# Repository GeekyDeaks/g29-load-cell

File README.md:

# G29 Load Cell Mod

Modification to replace the stock brake pedal sensor on a Logitech G29 pedal set with a load cell,
the purpose of which is to more closely simulate a real brake system which is dependent on
the force applied to the pedal and not the pedal position

I assume this would work on the G920 without any issues, and possibly the G27 and G25,
however I have not had the opportunity to test.

It uses a cheap load cell with two closely matched 1k resistors arranged in a
[Wheatstone bridge](https://en.wikipedia.org/wiki/Wheatstone_bridge)
and an Instrumentation Op-Amp.  The cell is mounted in a 3D printed
model that replaces the lower half of the brake piston assembly

There is a digital version by [SkiDude88](https://github.com/Skidude88/Skidude88-G29-PS4-LoadCell-Arduino/wiki) 
using an HX711, that often comes bundled with the load cells, and an Arduino

Assembly re-uses the spring and rubber block, along with a short piece of M10 rod.
The adjustment of the location of the washer and the protrusion of the top nut
allow changes to the first stage of the pedal, which is designed to simulate
the initial feel of the pedal as the pads move into contact with the disc.

Fully installed, with the amplifier circuit mounted in a small case

2020-10-22 UPDATE

Working on a 3D printed plunger to remove the need to cobble one together

# Shopping list

1. 3D printer capable of 80mm x 43mm x 43mm
2. Bathroom scale type loadcells
3. PCB copper board or stripboard (35mm x 30mm)
4. INA122P instrumentation amplifier
5. 1k trim pot
6. 10ohm trim pot 
7. 2x 1k resistor
8. 100ohm resistor (fake clutch)
9. 900ohm resistor (fake clutch)
10. M10 thread ~30mm
11. 3x Half height M10 nuts
12. 1x M10 nut
13. M10 to 24mm washer

# Software used

1. EAGLE https://www.autodesk.co.uk/products/eagle/free-download
2. Fusion 360 https://www.autodesk.com/campaigns/fusion-360-for-hobbyists

# Load Cells

The load cells are cheap bathroom scale variety.  I got mine from Amazon:

https://www.amazon.co.uk/gp/product/B07TWLP3X8

Each cell is comprised of two resistors one which increases under load (white) and the 
other which decreases (black).  Zero load is approx 1k, with about 2-3 Ohm change under heavy load

# Amplifier Circuit

The loadcell is connected to the circuit as follows:

1. Red -> 3.3v
2. Black -> V+
3. White -> V-

Since we need to output a higher voltage with no load on the cells 
we have to unbalance the bridge so that load brings it back into balance.

The 1k resistors for `R1` and `R2` should be measured and the larger of the two should
be used for `R1` to allow `R_BAL1` to adjust the link with `R2` and force the bridge out of 
balance with no load

`R_REF` should be replaced with a link from the middle pin to the right pin.  This
will tie the `REF` pin on the INA122P to ground.
It was originally used when the design had two load cells
and the INA122P was inverting the gain.

Astute observers may have noticed the connections for the loadcell appear to be
reversed in reference to V+ and V-.  This is because the labelling on the PCB of 
V+ and V- was in reference to the dual load cell configuration and hence the 
labels on the PCB are not correct for a single cell.

## Clutch

The circuit also allows for simulating a clutch, allowing it to be removed if desired.
The G29 has been known to glitch if the clutch is disconnected and the leads left hanging.

If you do not need this feature, you can leave `R3` and `R4` unpopulated on the board

# PCB

The PCB design is a little tricky to manually etch, so we came up with a slightly
larger design to help.  Note that this is a mirror image to print and apply to
the copper via toner transfer.  You can find a pdf with the correct size [here](pcb/load_cell_amp_diy.pdf)

# STL model

Previous prints have been done with the model on it's side.  This was to ensure the grain
in the upper cylinder was along the length of the cylinder

- 30% infill
- 5% support

[stl/single_holder.stl](stl/single_holder.stl)

The plunger is comprised of several sections.  It is recommened to print the bottom section with 100% infill

- [stl/plunger_bottom.stl](stl/plunger_bottom.stl)
- [stl/plunger_spacer_5mm.stl](stl/plunger_spacer_5mm.stl)
- [stl/plunger_spacer_10mm.stl](stl/plunger_spacer_10mm.stl)
- [stl/plunger_spacer_15mm.stl](stl/plunger_spacer_15mm.stl)
- [stl/plunger_top.stl](stl/plunger_top.stl)

# G29 brake levels

From reading around it seems that there is not an agreed set of values for what represents
min and max braking.  Below is a table I took from attaching an AVO directly to the middle pin 
of the brake potentiometer on my set and monitoring the output on the PS4:

| Level | Voltage |
|------:|---------|
| 0%    | 3.0     |
| 25%   | 2.5     |
| 50%   | 2.2     |
| 75%   | 2.0     |
| 100%  | 1.9     |

# Pedal Pin Outs

    -----------------------
    \  1   2   3   4   5  /
     \   6   7   8   9   /
       -----------------

| Pin | Role      | Colour
| --- | --------- | ------
| 1   | Gnd       | Black
| 2   | Throttle  | Orange
| 3   | Brake     | White
| 4   | Clutch    | Green
| 5   | NC        |
| 6   | +3.3v     | Red
| 7   | NC        |
| 8   | NC        |
| 9   | +3.3v     | Red

The above values were taken by removing the wiring loom from the pedal set
and measuring at the spade connectors.
Note that these pin outs are different to those reported by others for the G27
with +3.3v and Gnd switched

# Inspiration

This is a popular mod and others have come before with interesting designs that you may also
want to take a look at:

- https://www.reddit.com/r/simracing/comments/92exmk/diy_load_cell_brake_for_g29_with_native_ps4/
- https://www.racedepartment.com/threads/low-budget-load-cell-mod-for-logitech-g25-g27-g29.167760/
- https://imgur.com/gallery/gOjAf#SXX5zrY
- https://www.racedepartment.com/threads/logitech-g25-g27-g29-g920-load-cell-diy-project.174623/

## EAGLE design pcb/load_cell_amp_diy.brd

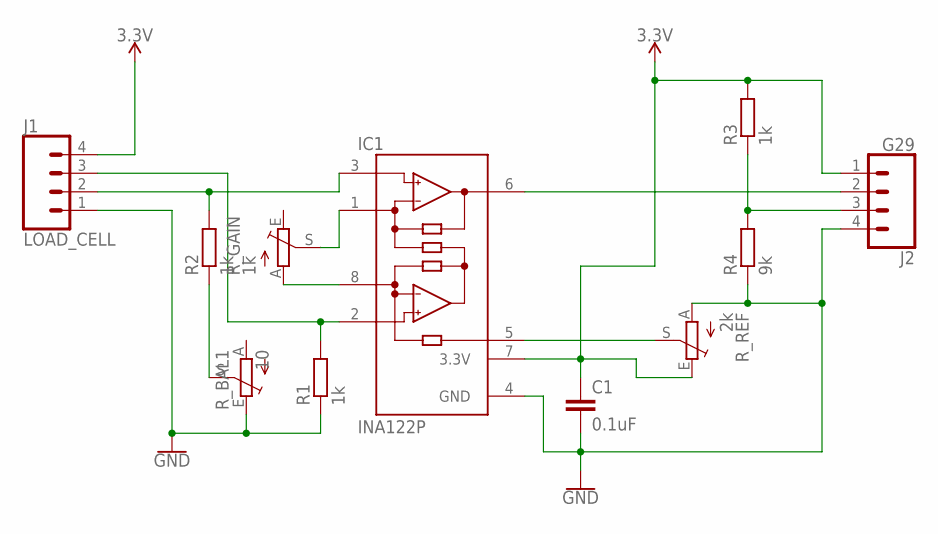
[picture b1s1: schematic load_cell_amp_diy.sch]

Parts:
C1: 0.1uF; C2.5-3
IC1: INA122P; DIL08
J1: LOAD_CELL; 04P
J2: G29; 04P
R1, R2, R3: 1k; 0207/10
R4: 9k; 0207/10
R_BAL1: 10; RJ9W
R_GAIN: 1k; RJ9W
R_REF: 2k; RJ9W

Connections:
3.3V: C1.1, IC1.7 (3.3V), J1.4, J2.1, R3.2, R_REF.E
CLUTCH: IC1.6 (OUT), J2.2
GND: C1.2, IC1.4 (GND), J1.1, J2.4, R1.1, R4.1, R_BAL1.E, R_REF.A
unnamed: IC1.8 (RG), R_GAIN.A
unnamed: IC1.1 (RG), R_GAIN.S
unnamed: IC1.3 (+IN), J1.2, R2.2
unnamed: IC1.2 (-IN), J1.3, R1.2
unnamed: R2.1, R_BAL1.S
unnamed: IC1.5 (REF), R_REF.S
unnamed: J2.3, R3.1, R4.2

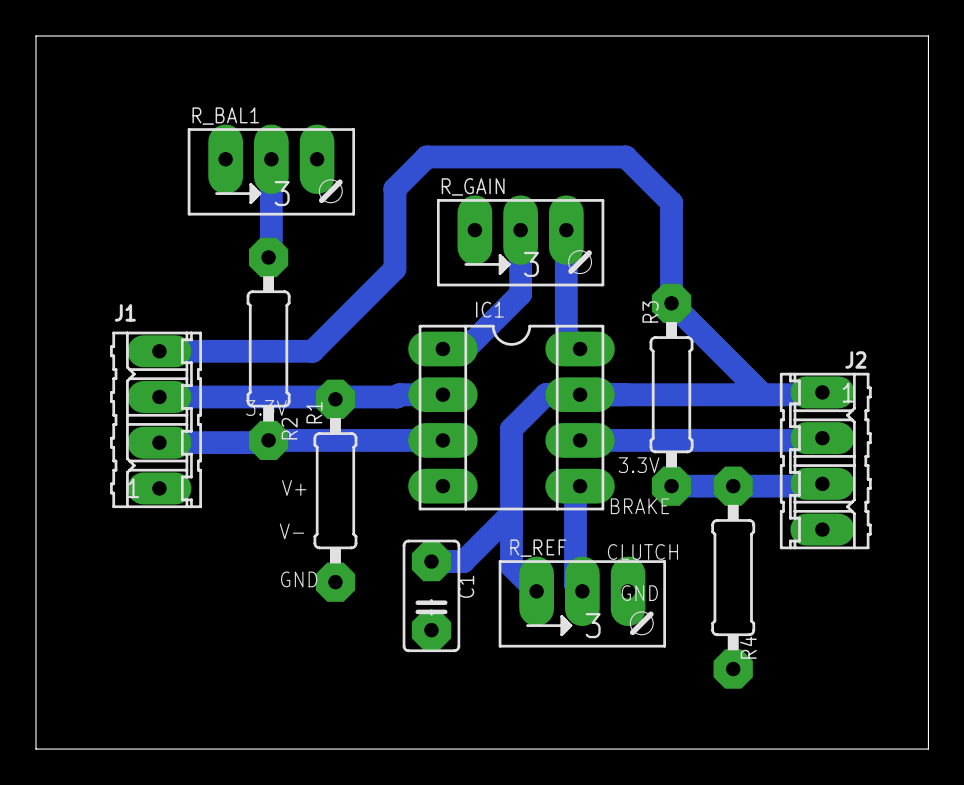
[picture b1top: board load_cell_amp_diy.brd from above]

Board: 2 copper layers, 49.6 x 39.6 mm, 11 parts (0 on the bottom side), 10 nets.

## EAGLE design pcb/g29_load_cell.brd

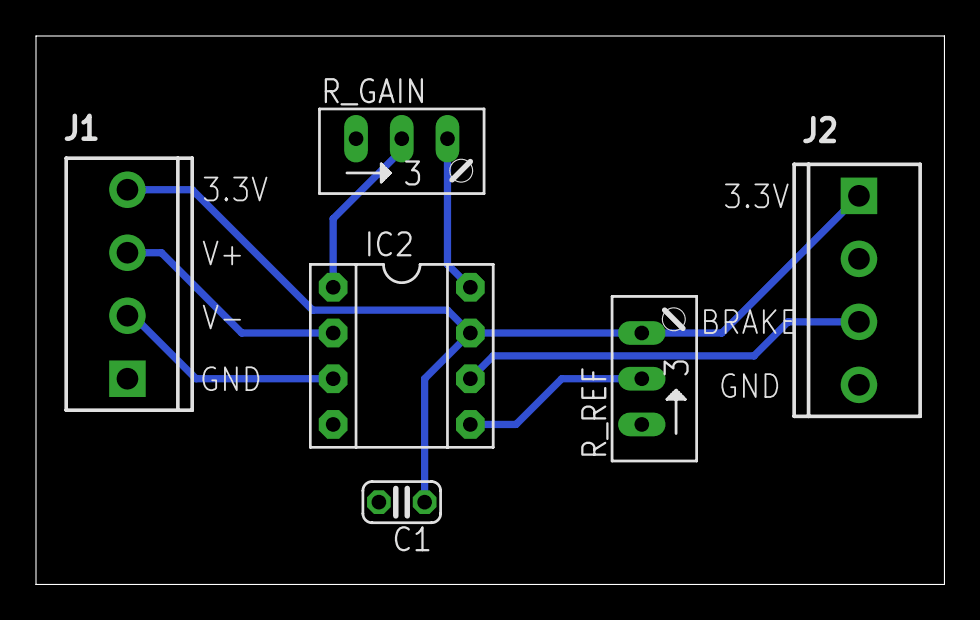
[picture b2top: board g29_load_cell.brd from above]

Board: 2 copper layers, 50.5 x 30.5 mm, 6 parts (0 on the bottom side), 8 nets.

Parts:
C1: 0.1uF; C025-024X044
IC2: INA122P; DIL08
J1: LOAD_CELL; SCREWTERMINAL-3.5MM-4
J2: G29; SCREWTERMINAL-3.5MM-4
R_GAIN: 1k; RJ9W
R_REF: 2k; RJ9W

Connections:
3.3V: C1.1, IC2.7, J1.4, J2.1, R_REF.A
GND: C1.2, IC2.4, J1.1, J2.4, R_REF.E
unnamed: IC2.8, R_GAIN.A
unnamed: IC2.1, R_GAIN.S
unnamed: IC2.3, J1.2
unnamed: IC2.2, J1.3
unnamed: IC2.5, R_REF.S
unnamed: IC2.6, J2.3

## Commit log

2019-12-24 fixed ERC errors
2019-12-24 renamed PCB and schematic
2019-12-24 renamed eagle project lib
2019-12-26 added stl files for cell holder
2019-12-26 fixed links to stl files
2019-12-26 second attempt to fix stl links
2019-12-26 edits to readme
2019-12-26 added loadcell spec
2019-12-26 updated description
2019-12-27 updated holder model
2019-12-27 added cell retainer to holder model
2019-12-27 typo in readme
2019-12-27 added links to other designs
2019-12-27 hide retainer
2019-12-27 added schematic image
2019-12-28 renamed IC2 to IC1
2019-12-28 updated schematic image
2019-12-30 tweaked holder model
2019-12-30 updated links to be bulleted
2020-01-04 updated schematic to support single cell
2020-01-04 added single cell model
2020-01-04 fixed dual spacer model link
2020-01-05 updated single cell model
2020-01-08 DIY PCB board for etching
2020-01-10 updated diy board to help etching and soldering
2020-02-13 updated images
2020-02-23 increased spring guide diameter
2020-02-23 v3 pics and updates
2020-02-23 diy pcb image
2020-02-23 readme formatting
2020-02-23 typo
2020-02-23 spell check
2020-02-23 diy pcb updates
2020-10-22 added plunger scad
2020-10-22 add plunger

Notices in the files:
parts and their libraries:
SparkFun-Connectors: Licensing: Creative Commons ShareAlike 4.0 International - https://creativecommons.org/licenses/by-sa/4.0
